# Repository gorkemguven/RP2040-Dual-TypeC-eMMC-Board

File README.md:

# RP2040 Dual Type-C eMMC High-Speed Development & Telemetry Board (PicoVault)

Bu proje; **Raspberry Pi RP2040** çift çekirdekli mikrodenetleyicisi, **Microchip USB2244** yüksek hızlı USB 2.0 köprüsü ve **Micron eMMC (BGA-153)** yüksek yoğunluklu depolama birimini tek bir 4 katmanlı PCB üzerinde birleştiren endüstriyel standartta bir akıllı veri depolama ve geliştirme kartıdır.

Kart; çift USB Type-C mimarisi, donanımsal güç telemetrisi (çift INA226 akım/voltaj monitörü ve Kelvin algılama), yüksek doğruluklu sıcaklık izleme (TMP119) ve durum bilgilendirme OLED ekran arayüzü ile hem bağımsız bir yüksek hızlı USB flash sürücü hem de derinlemesine analiz yapabilen bir gömülü geliştirme platformu olarak tasarlanmıştır.

---

## 📌 Öne Çıkan Özellikler

* **Çift Çekirdekli İşlem Gücü:** Raspberry Pi RP2040 (Çift ARM Cortex-M0+ @ 133 MHz, 264 KB dahili SRAM).
* **Yüksek Hızlı Depolama (eMMC):** Micron BGA-153 paket yüksek hızlı eMMC bellek modülü.
* **Yüksek Hızlı USB Köprüsü:** Microchip USB2244 High-Speed USB 2.0 SD/eMMC kontrolcüsü (480 Mbps).
* **Boot Flash Belleği:** 128 Mb (16 MB) Winbond W25Q128JVSIC QSPI Flash[cite: 3].
* **Çift USB Type-C Portu:**
  * *Port 1 (Depolama):* USB2244 üzerinden doğrudan eMMC'ye yüksek hızlı USB 2.0 (480 Mbps) erişim.
  * *Port 2 (MCU / Telemetri):* RP2040 Full-Speed USB arayüzü (veri kaydı, programlama, seri haberleşme).
* **Donanımsal Güç ve Sıcaklık Telemetrisi:**
  * 2x **TI INA226** I2C güç/gerilim/akım izleme entegresi (2 mΩ 4-terminalli Kelvin şönt algılama)[cite: 7, 8].
  * 1x **TI TMP119** ±0.1°C yüksek hassasiyetli dijital sıcaklık sensörü[cite: 4].
  * 0.96'' I2C SSD1306 OLED ekran konnektörü ile anlık telemetri gösterimi[cite: 5].
* **Genişleme Portu:** Harici SPI, I2C, UART ve GPIO erişimi sağlayan 12-pin breakout soketi[cite: 1].
* **Üretim Optimizasyonu:** Maliyet düşürmek amacıyla tüm kritik bileşenler tek yüzeye (Single-Sided Assembly) yerleştirilmiştir.

---

## 📐 Donanım Mimarisi ve Yüksek Hızlı Sinyal Bütünlüğü

### 1. USB2244 – eMMC (BGA-153) 8-Bit Yüksek Hızlı Veri Yolu (Zero-Skew Matching)
USB2244 ile eMMC arasındaki 8-bit paralel veri yolu (MMC standardı), yüksek frekanslı çalışma modlarında saat ve veri gecikmelerini (skew) sıfırlamak için **tam 35.66 mm** boyuna meander teknikleriyle kusursuz şekilde eşitlenmiştir:
* **Tüm Hatların Uzunluğu:** Tam olarak **35.66 mm**
* **Maksimum Skew / Sapma:** **0.00 mm (0.00 ps)**
* **Hat Empedansı:** Katman 2 kesintisiz GND referansı üzerinden 50 Ω mikroşerit geometri.

| Sinyal Adı | Pin Adı | Rotalama Türü | Empedans | Net Hat Uzunluğu | Skew (Fark) |
| :--- | :--- | :--- | :---: | :---: | :---: |
| **`MMC_CLK`** | Clock (Saat) | GND Referanslı Mikroşerit | 50 Ω | **35.66 mm** | Referans |
| **`MMC_CMD`** | Command / Response | Çift Yönlü Kontrol | 50 Ω | **33.44 mm** | **2.22 mm** |
| **`MMCDA0`** | Data Bit 0 | Yüksek Hızlı Veri | 50 Ω | **35.66 mm** | **0.00 mm** |
| **`MMCDA1`** | Data Bit 1 | Yüksek Hızlı Veri | 50 Ω | **35.66 mm** | **0.00 mm** |
| **`MMCDA2`** | Data Bit 2 | Yüksek Hızlı Veri | 50 Ω | **35.66 mm** | **0.00 mm** |
| **`MMCDA3`** | Data Bit 3 | Yüksek Hızlı Veri | 50 Ω | **35.66 mm** | **0.00 mm** |
| **`MMCDA4`** | Data Bit 4 | Yüksek Hızlı Veri | 50 Ω | **35.56 mm** | **0.10 mm** |
| **`MMCDA5`** | Data Bit 5 | Yüksek Hızlı Veri | 50 Ω | **35.66 mm** | **0.00 mm** |
| **`MMCDA6`** | Data Bit 6 | Yüksek Hızlı Veri | 50 Ω | **35.66 mm** | **0.00 mm** |
| **`MMCDA7`** | Data Bit 7 | Yüksek Hızlı Veri | 50 Ω | **35.66 mm** | **0.00 mm** |
| **`MMC_RST_N`** | Hardware Reset | Filtrelenmiş Kontrol | 50 Ω | Bağımsız | Asenkron |

*(Not: Bu 10 hattın tamamında sıfır kör hat (stub-free) prensibi uygulanmış ve BGA çıkışlarında dönüş akımının bütünlüğü korunmuştur).*

### 2. QSPI Flash Yönlendirme ve Gecikme Eşleme (Length Matching)
Flash bellek yolu, 133 MHz saat hızında okuma/yazma kararlılığını garanti altına almak için 50 Ω kontrollü empedans ve katı boy eşleme kurallarıyla yönlendirilmiştir:
* **Tüm Sinyal Hatları:** Eşit parazitik yük için tam olarak **2 via** kullanılarak alt katmana geçirilmiştir.
* **Saat Hattı Referansı (`QSPI_SCLK`):** 24.54 mm
* **Veri Hatları Skew Dengesi:**
  * `QSPI_SD0`: 26.10 mm (ΔL = +1.56 mm)
  * `QSPI_SD1`: 25.76 mm (ΔL = +1.22 mm)
  * `QSPI_SD2`: 27.14 mm (ΔL = +2.60 mm)
  * `QSPI_SD3`: 24.81 mm (ΔL = +0.27 mm)
  * `QSPI_SS`: 22.57 mm (ΔL = -1.97 mm)
* **Stub İzolasyonu:** 1 kΩ (`R504`) BOOTSEL izolasyon direnci ve 10 kΩ (`R505`) pull-up direnci, yüksek hızlı `/CS` hattında açık devre yansıması oluşturmaması için doğrudan Flash entegresinin Pin 1 bacağının 1 mm yakınına konumlandırılmıştır[cite: 3].

### 3. Analog Kristal Osilatör Bölgesi (EMC & Noise Immunity)
* **Rezonatör:** RP2040 için 12 MHz SMD kristal ve 15 pF yük kapasitörleri.
* **Sönümleme:** `XOUT` bacağında 1 kΩ seri akım sınırlama/sönümleme direnci.
* **Gürültü Koruması (Keepout Area):** Kristalin ve yük kapasitörlerinin altındaki tüm katmanlar dijital sinyallerden arındırılmıştır[cite: 2]. `SPI_SCK` ve hızlı GPIO hatları kristal sınırının dışına taşınmış; Layer 2 üzerinde kesintisiz katı GND bakırı ve kristal gövde pinlerinde (Pin 2 ve 4) çift via topraklaması uygulanmıştır[cite: 2].

### 4. eMMC Güç Dağıtım Ağı (PDN - Decoupling Network)
* Tek yüzeyli montaj gereği dekuplaj kapasitörleri BGA-153 paketinin çevresine optimize mesafelerle dizilmiştir:
  * **VDDIM (`C2`):** 4.6 mm hat, 2 via, 100 nF + 1 µF çift filtreleme.
  * **VCC (`E6, F5` & `J10, K9`):** 100 nF, 1 µF ve 2.2 µF kapasitör grupları (6.5–8.0 mm).
  * **VCCQ (`C6` & `M4, N4, P3, P5`):** Çekirdek VCC hattındaki anahtarlama gürültüsünden etkilenmemesi için yüzeyde VCC'den izole edilmiş; ana +3.3V düzleminden yerel 2.2 µF kapasitörlerle beslenmiştir.

### 5. Kelvin Akım Algılama ve I2C Topolojisi
* **4-Wire Kelvin Sensing:** 2 mΩ şönt dirençlerin gerilim algılama pinleri (`IN+` ve `IN-`), yüksek akım taşıyan güç pedlerinden bağımsız olarak alt katmandan diferansiyel çift mantığıyla INA226 entegrelerine taşınmıştır[cite: 7, 9].
* **Adresleme:**
  * `IC702` (INA226 #1): A1 = GND, A0 = GND → **0x40**[cite: 8]
  * `IC703` (INA226 #2): A1 = GND, A0 = +3.3V → **0x41**[cite: 8]
* **I2C Veriyolu:** RP2040'tan çıkan tek veriyolu TMP119 (3.5 cm), OLED (5.3 cm), INA1 (7.0 cm) ve INA2 (8.8 cm) arayüzlerini beslemektedir[cite: 4, 5, 8]. Hat empedansı TMP119 yakınındaki 5 kΩ pull-up dirençleri (`R701`, `R702`) ile sürülmekte ve toplam veriyolu kapasitansı 400 pF standardının oldukça altında kalmaktadır[cite: 4, 6].

---

## 🔌 Bağlantı Portları ve Pin Şeması

### 1. J803 Genişleme Konnektörü (1x12 Pin Header)
Harici çevre birimleri ve geliştirme modülleri için dışarı çıkarılmış arayüzdür[cite: 1]:

| Pin | Sinyal Adı | Tip | Rotalama Detayı | Açıklama |
| :---: | :--- | :--- | :--- | :--- |
| **1** | `+3.3V` | Güç | Çift via ile +3.3V katmanına bağlı | Harici modül beslemesi |
| **2** | `UART_TX` | Çıkış | 50.00 mm (0 via) | Seri konsol / Debug çıkışı |
| **3** | `UART_RX` | Giriş | 49.80 mm (0 via) | Seri konsol giriş |
| **4** | `SPI_SCK` | Çıkış | 42.17 mm (2 via) | Harici SPI Saat hattı |
| **5** | `SPI_MOSI` | Çıkış | 41.52 mm (2 via) | Harici SPI Veri çıkışı |
| **6** | `SPI_MISO` | Giriş | 41.83 mm (2 via) | Harici SPI Veri girişi |
| **7** | `SPI_CS` | Çıkış | 41.92 mm (2 via) | Harici SPI Çip seçimi |
| **8** | `I2C_SDA` | Çift Yönlü | 57.08 mm (2 via) | Harici I2C Veri hattı |
| **9** | `I2C_SCL` | Çıkış | 56.62 mm (2 via) | Harici I2C Saat hattı |
| **10** | `GPIO14` | Giriş/Çıkış | 43.70 mm (2 via) | Genel amaçlı GPIO / Kesme |
| **11** | `GPIO15` | Giriş/Çıkış | 43.87 mm (2 via) | Genel amaçlı GPIO / Kesme |
| **12** | `GND` | Güç | Çift via ile ana GND katmanına bağlı | Ortak sistem toprağı |

*(Not: SPI veri yolu hatları arasındaki maksimum skew yalnızca 0.65 mm'dir; bu sayede yüksek hızlı SPI ekranlar veya harici modüllerle sorunsuz çalışır).*

### 2. Programlama ve Hata Ayıklama (Debug)
* **SWD Portu (`SWCLK`, `SWD`, `GND`):** Canlı hata ayıklama (step-by-step breakpoint debug) ve doğrudan bellek programlama arayüzüdür.
  * `SWCLK` (22.60 mm) ve `SWD` (23.00 mm) hatları tam simetrik ve 0.40 mm toleransla eşlenmiştir.
* **RUN (Donanımsal Reset):** 100 nF kapasitör ve 10 kΩ pull-up direnci ile çipin 3.66 mm dibinde filtrelenmiştir.
* **J502 (`USB_BOOT`):** 1 kΩ direnç üzerinden Flash `/CS` hattını toprağa çekerek RP2040'ı dahili ROM UF2 Mass Storage bootloader moduna geçirir[cite: 3].

---

## 🗂️ Depo Dosya Yapısı

```text
├── hardware/
│   ├── schematics/          # KiCad hiyerarşik şematik dosyaları (.kicad_sch)
│   ├── layout/              # KiCad 4-katman PCB yerleşim dosyaları (.kicad_pcb)
│   ├── libraries/           # Projeye özel kütüphane sembol ve ayak izleri (Footprints)
│   └── outputs/
│       ├── gerbers/         # Üretim için RS-274X Gerber ve Drill dosyaları
│       └── bom/             # Parça listesi (Bill of Materials - .csv)
├── docs/
│   ├── schematics.pdf       # Tek tıkla incelenebilir tam şematik PDF çıktısı
│   ├── 3d_renders/          # Kartın ön/arka 3D görsel renderları
│   └── datasheets/          # Kritik entegre dökümanları (USB2244, INA226, TMP119, W25Q128)
├── .gitignore               # KiCad geçici ve yedek dosyalarını filtreler
└── README.md                # Proje dokümantasyonu

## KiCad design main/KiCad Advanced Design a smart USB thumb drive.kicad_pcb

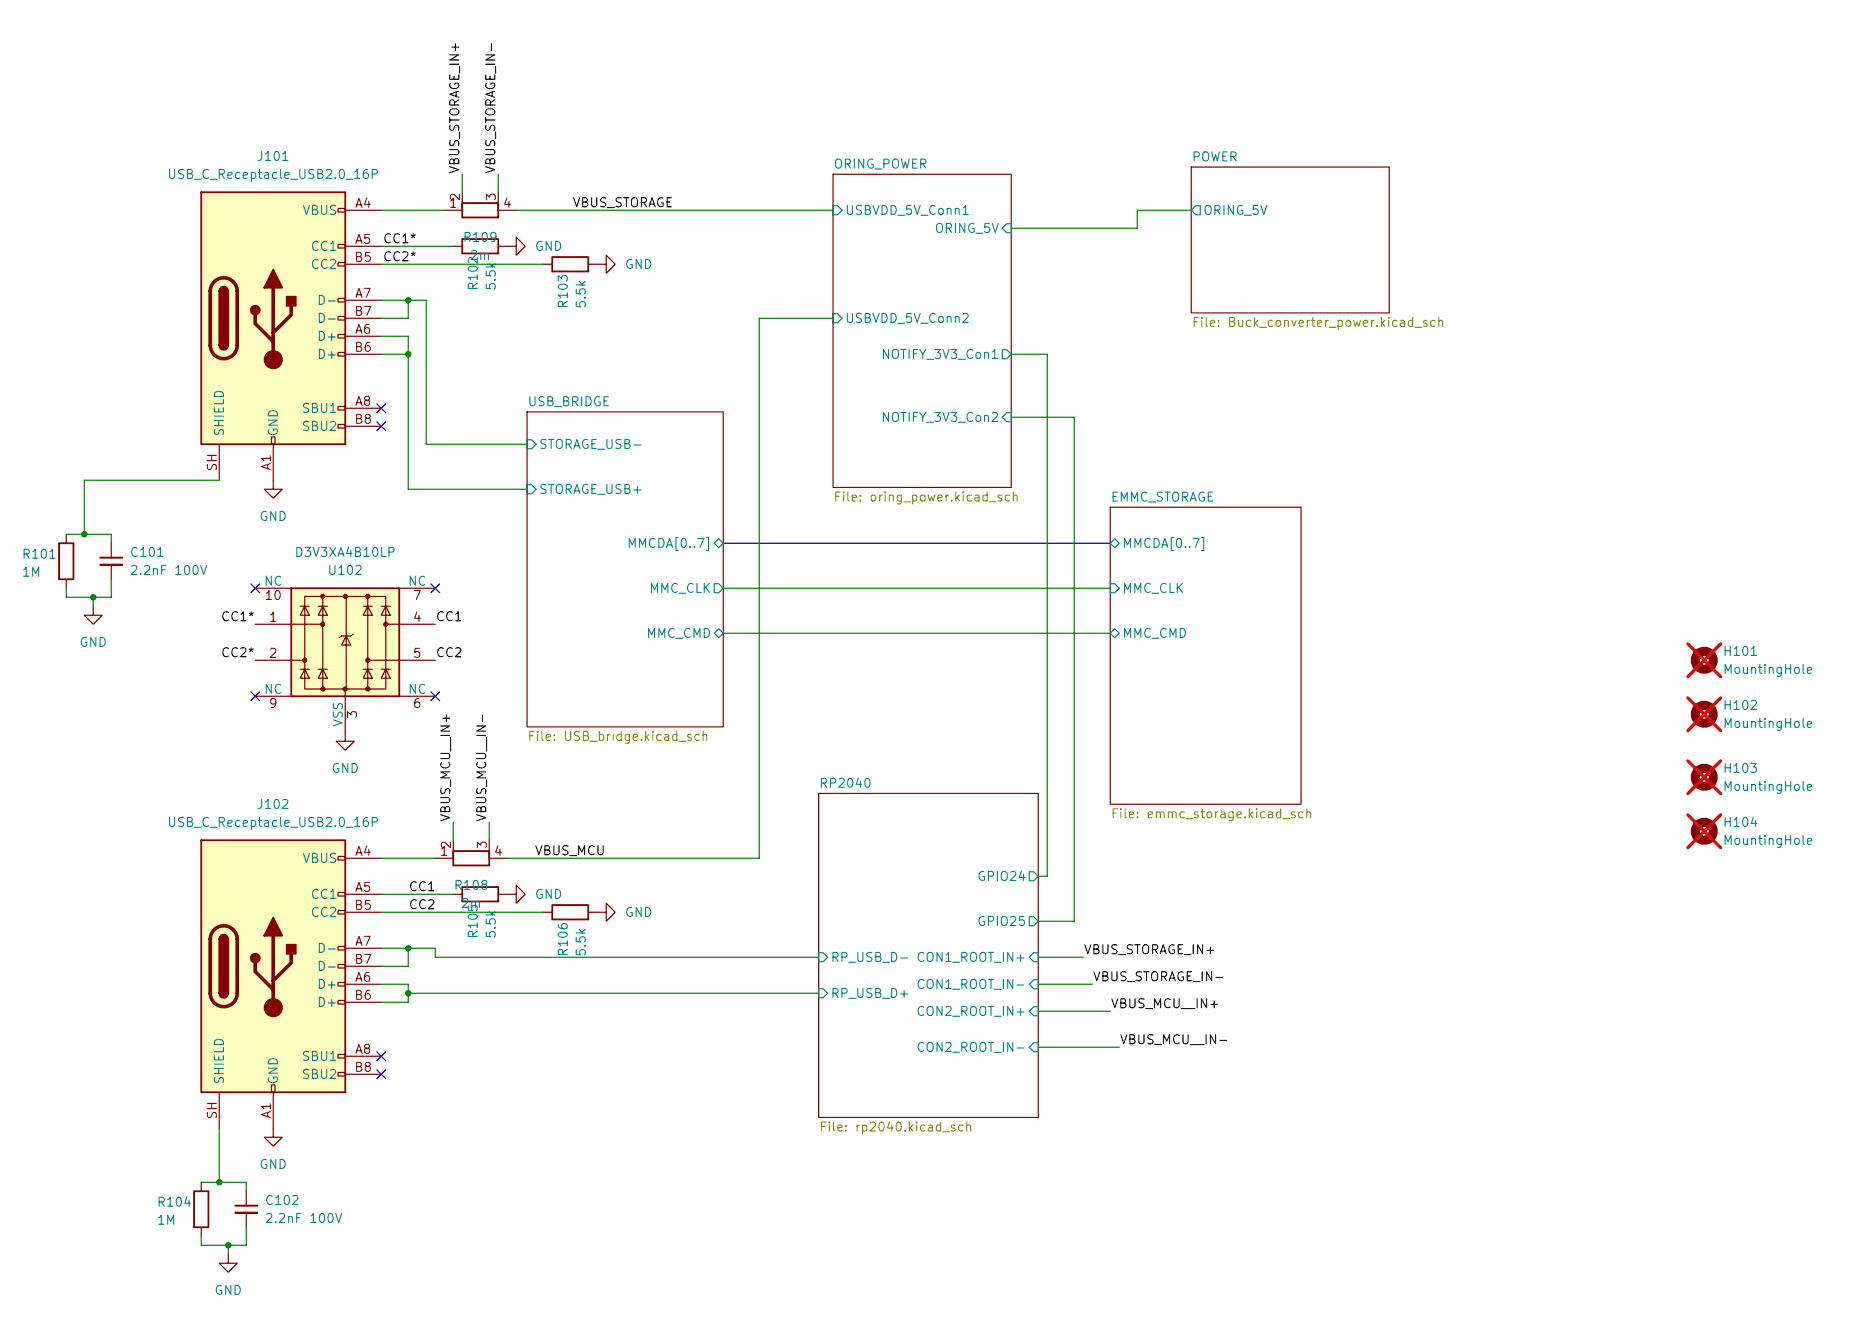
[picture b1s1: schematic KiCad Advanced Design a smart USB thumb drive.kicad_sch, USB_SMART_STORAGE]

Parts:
C101, C102: 2.2nF 100V; C_0603_1608Metric
H101, H102, H103, H104: MountingHole; MountingHole_2.2mm_M2; not fitted
J101, J102: USB_C_Receptacle_USB2.0_16P; USB_C_Receptacle_XKB_U262-16XN-4BVC11
R101, R104: 1M; R_0402_1005Metric
R102, R103, R105, R106: 5.5k; R_0402_1005Metric
R108, R109: 2m; R_Shunt_Ohmite_LVK12
U102: D3V3XA4B10LP; Diodes_UDFN-10_1x2.5mm_P0.5mm

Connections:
/CC1: J102.A5 (CC1), R105.1, U102.4
/CC1*: J101.A5 (CC1), R102.1, U102.1
/CC2: J102.B5 (CC2), R106.1, U102.5
/CC2*: J101.B5 (CC2), R103.1, U102.2
/RP2040/RP_USB_D+: J102.A6 (D+), J102.B6 (D+); also elsewhere on the board
/RP2040/RP_USB_D-: J102.A7 (D-), J102.B7 (D-); also elsewhere on the board
/USB_BRIDGE/STORAGE_USB+: J101.A6 (D+), J101.B6 (D+); also elsewhere on the board
/USB_BRIDGE/STORAGE_USB-: J101.A7 (D-), J101.B7 (D-); also elsewhere on the board
/VBUS_MCU: R108.4; also elsewhere on the board
/VBUS_MCU__IN+: R108.2; also elsewhere on the board
/VBUS_MCU__IN-: R108.3; also elsewhere on the board
/VBUS_STORAGE: R109.4; also elsewhere on the board
/VBUS_STORAGE_IN+: R109.2; also elsewhere on the board
/VBUS_STORAGE_IN-: R109.3; also elsewhere on the board
GND: C101.2, C102.2, J101.A1 (GND), J101.A12 (GND), J101.B1 (GND), J101.B12 (GND), J102.A1 (GND), J102.A12 (GND), J102.B1 (GND), J102.B12 (GND), R101.2, R102.2, R103.2, R104.2, R105.2, R106.2, U102.3 (VSS), U102.8 (VSS); also elsewhere on the board
unnamed: C101.1, J101.SH (SHIELD), R101.1
unnamed: J101.A4 (VBUS), J101.A9 (VBUS), J101.B4 (VBUS), J101.B9 (VBUS), R109.1
unnamed: C102.1, J102.SH (SHIELD), R104.1
unnamed: J102.A4 (VBUS), J102.A9 (VBUS), J102.B4 (VBUS), J102.B9 (VBUS), R108.1

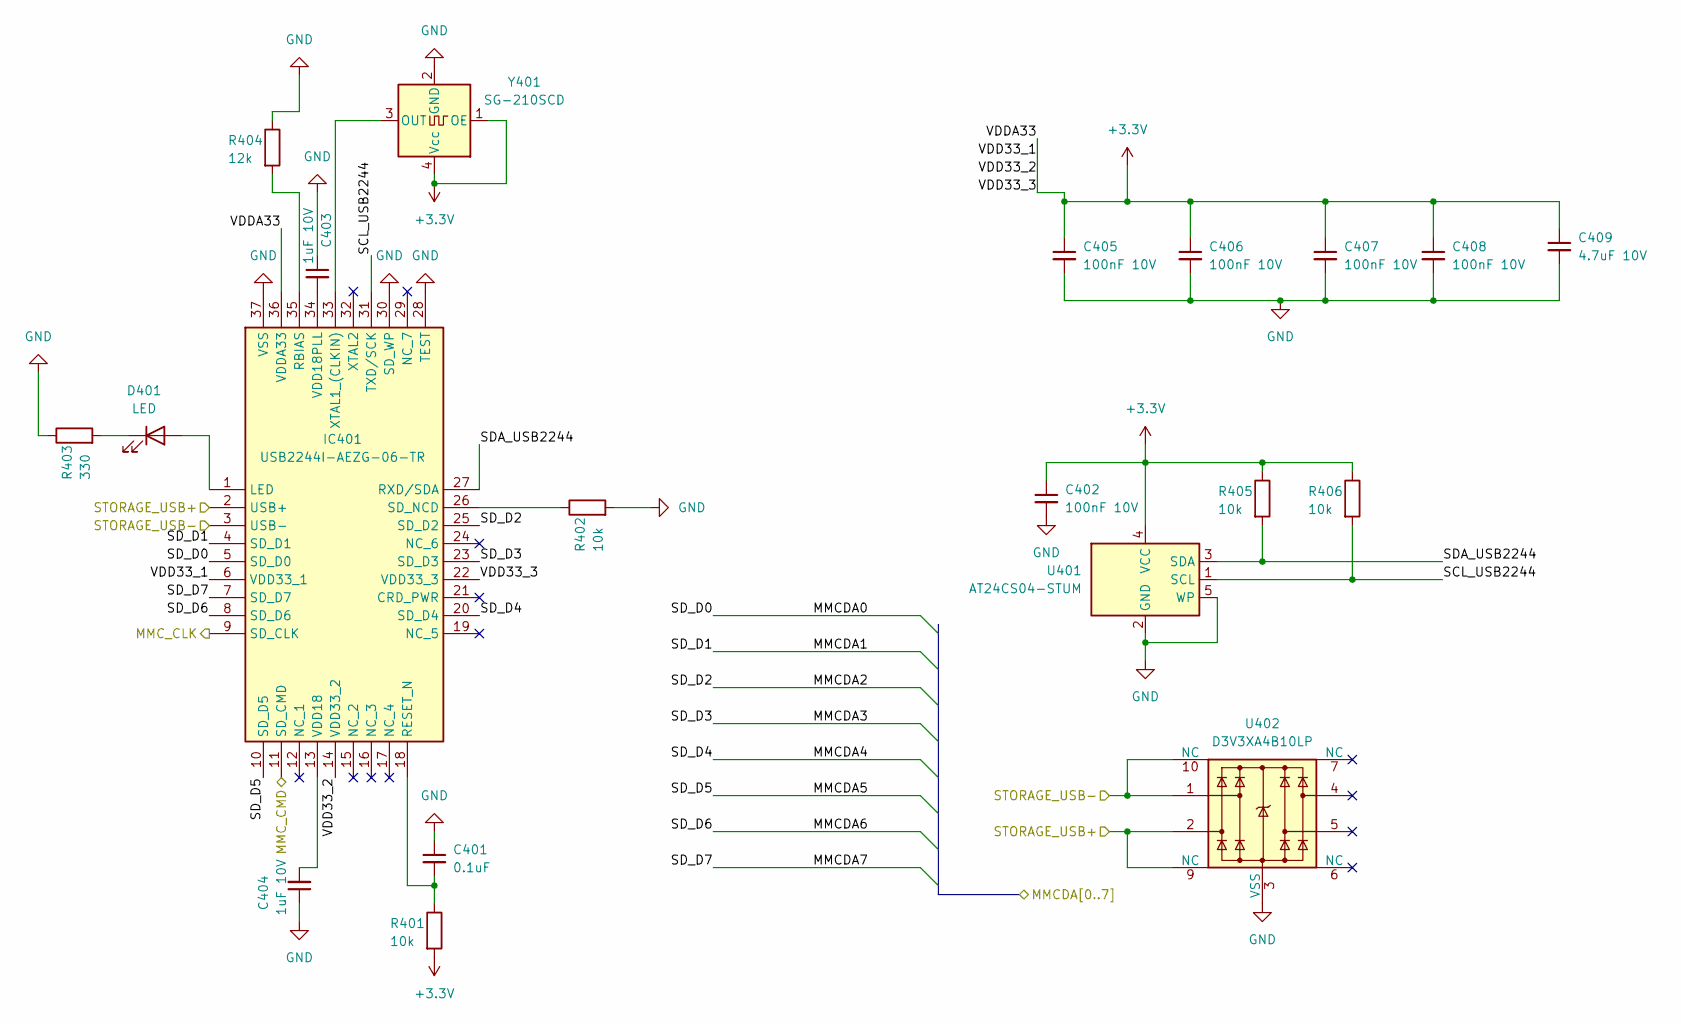
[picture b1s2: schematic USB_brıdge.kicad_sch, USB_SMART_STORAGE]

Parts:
C401: 0.1uF; C_0402_1005Metric
C402, C405, C406, C407, C408: 100nF 10V; C_0402_1005Metric
C403, C404: 1uF 10V; C_0603_1608Metric
C409: 4.7uF 10V; C_0603_1608Metric
D401: LED; LED_0603_1608Metric
IC401: USB2244I-AEZG-06-TR; QFN50P600X600X90-37N-D; Manufacturer_Part_Number USB2244I-AEZG-06-TR; Mouser Part Number 579-USB2244IAEZG06TR
R401, R402, R405, R406: 10k; R_0402_1005Metric
R403: 330; R_0402_1005Metric
R404: 12k; R_0402_1005Metric
U401: AT24CS04-STUM; SOT-23-5
U402: D3V3XA4B10LP; Diodes_UDFN-10_1x2.5mm_P0.5mm
Y401: SG-210SCD; Oscillator_SMD_SeikoEpson_SG210-4Pin_2.5x2.0mm

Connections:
+3.3V: C402.1, C405.1, C406.1, C407.1, C408.1, C409.1, IC401.6 (VDD33_1), IC401.14 (VDD33_2), IC401.22 (VDD33_3), IC401.36 (VDDA33), R401.2, R405.1, R406.1, U401.4 (VCC), Y401.1 (OE), Y401.4 (Vcc); also elsewhere on the board
/EMMC_STORAGE/MMCDA0: IC401.5 (SD_D0); also elsewhere on the board
/EMMC_STORAGE/MMCDA1: IC401.4 (SD_D1); also elsewhere on the board
/EMMC_STORAGE/MMCDA2: IC401.25 (SD_D2); also elsewhere on the board
/EMMC_STORAGE/MMCDA3: IC401.23 (SD_D3); also elsewhere on the board
/EMMC_STORAGE/MMCDA4: IC401.20 (SD_D4); also elsewhere on the board
/EMMC_STORAGE/MMCDA5: IC401.10 (SD_D5); also elsewhere on the board
/EMMC_STORAGE/MMCDA6: IC401.8 (SD_D6); also elsewhere on the board
/EMMC_STORAGE/MMCDA7: IC401.7 (SD_D7); also elsewhere on the board
/EMMC_STORAGE/MMC_CLK: IC401.9 (SD_CLK); also elsewhere on the board
/EMMC_STORAGE/MMC_CMD: IC401.11 (SD_CMD); also elsewhere on the board
/USB_BRIDGE/SCL_USB2244: IC401.31 (TXD/SCK), R406.2, U401.1 (SCL)
/USB_BRIDGE/SDA_USB2244: IC401.27 (RXD/SDA), R405.2, U401.3 (SDA)
/USB_BRIDGE/STORAGE_USB+: IC401.2 (USB+), U402.2, U402.9 (NC); also elsewhere on the board
/USB_BRIDGE/STORAGE_USB-: IC401.3 (USB-), U402.1, U402.10 (NC); also elsewhere on the board
GND: C401.1, C402.2, C403.1, C404.1, C405.2, C406.2, C407.2, C408.2, C409.2, IC401.28 (TEST), IC401.30 (SD_WP), IC401.37 (VSS), R402.2, R403.1, R404.1, U401.2 (GND), U401.5 (WP), U402.3 (VSS), U402.8 (VSS), Y401.2 (GND); also elsewhere on the board
unnamed: D401.2 (A), IC401.1 (LED)
unnamed: D401.1 (K), R403.2
unnamed: IC401.35 (RBIAS), R404.2
unnamed: C401.2, IC401.18 (RESET_N), R401.1
unnamed: IC401.26 (SD_NCD), R402.1
unnamed: C404.2, IC401.13 (VDD18)
unnamed: C403.2, IC401.34 (VDD18PLL)
unnamed: IC401.33 (XTAL1_(CLKIN)), Y401.3 (OUT)

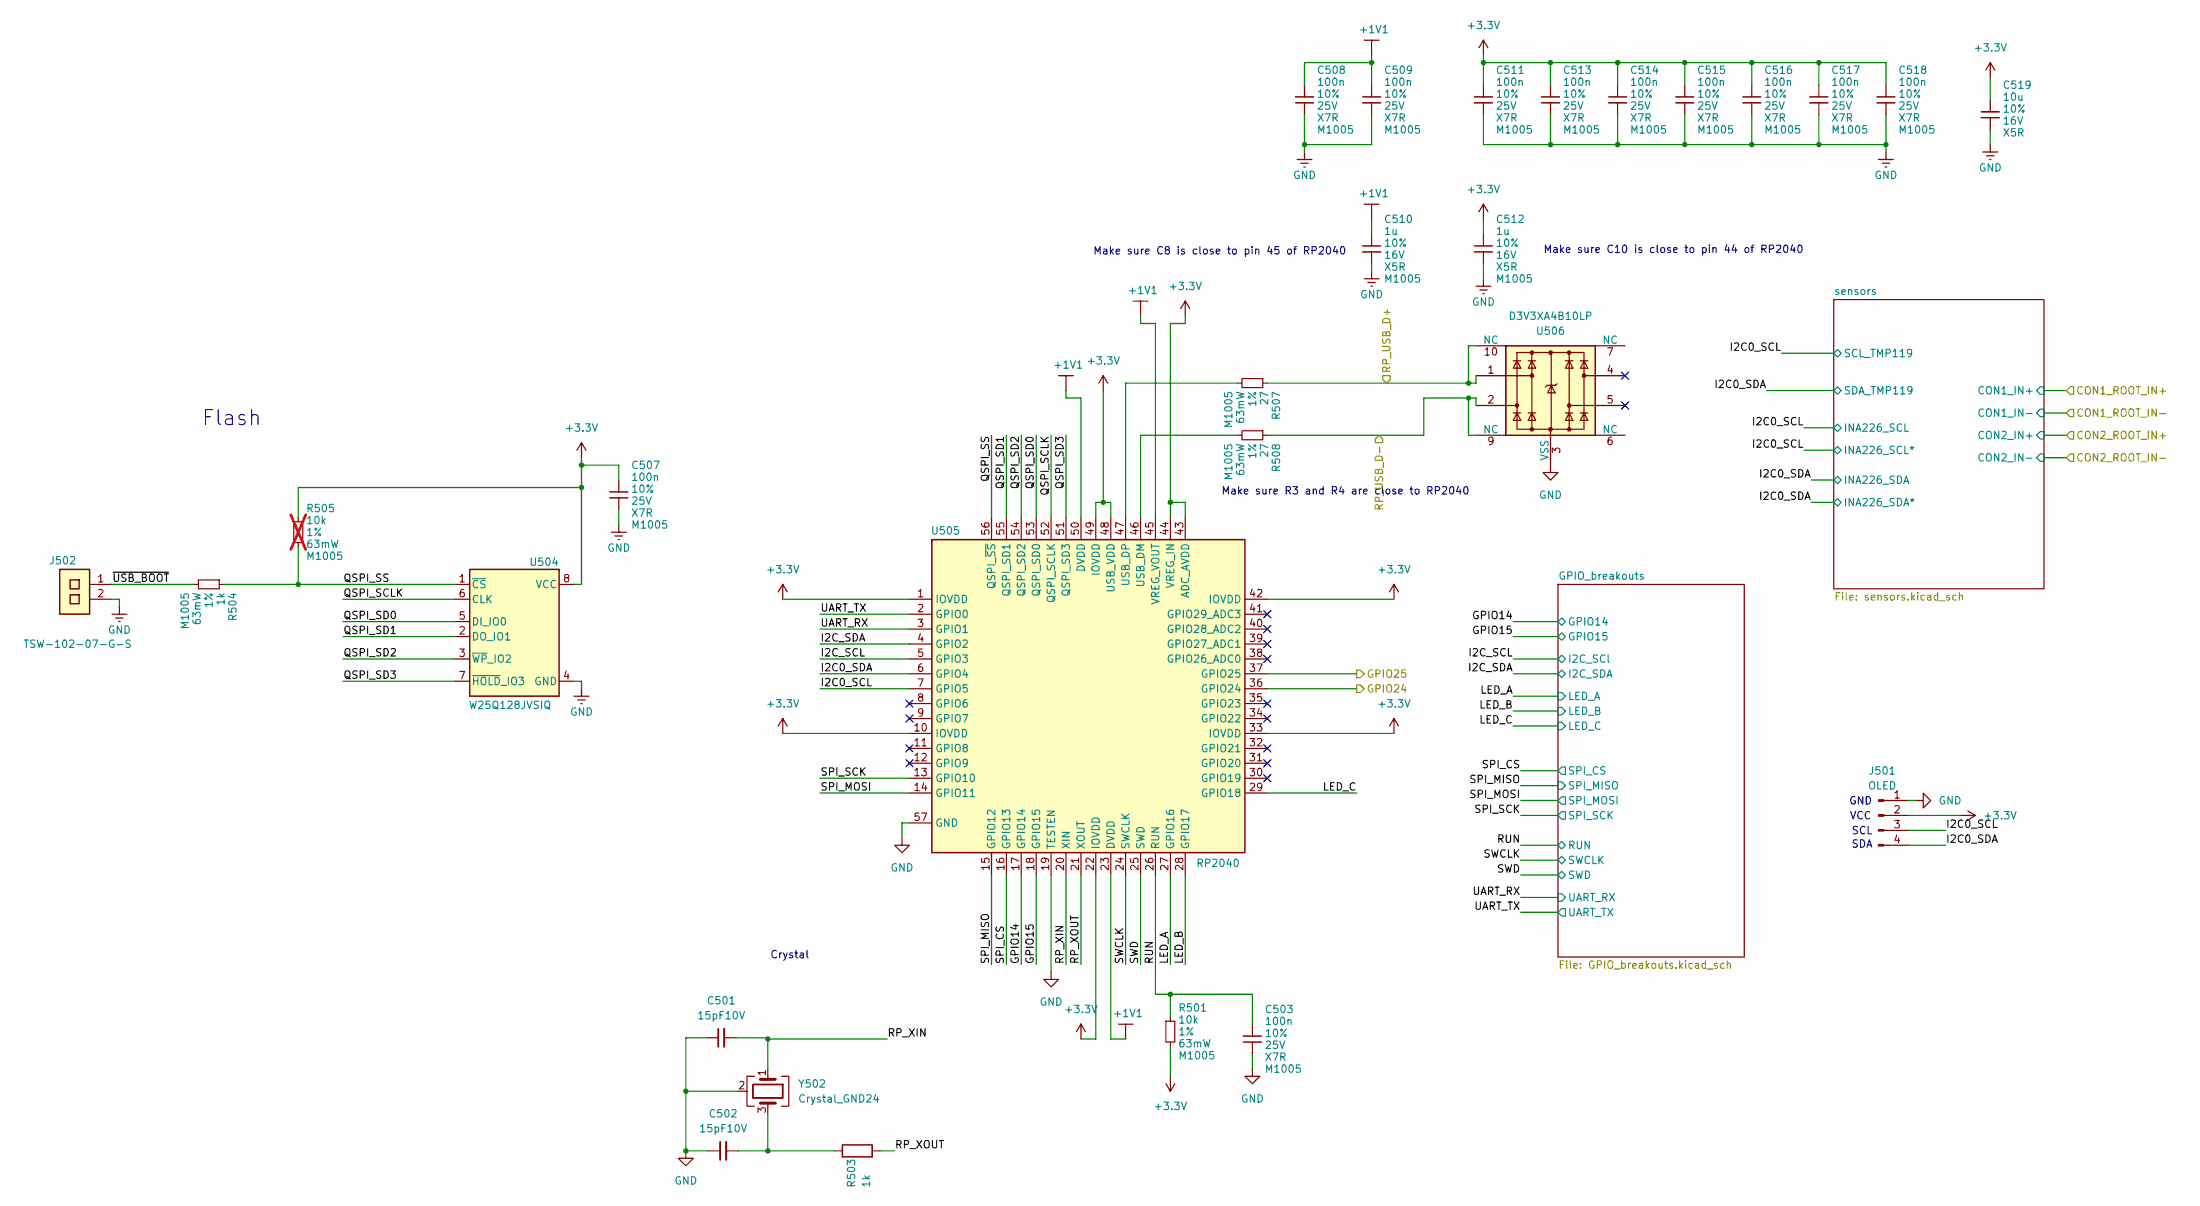
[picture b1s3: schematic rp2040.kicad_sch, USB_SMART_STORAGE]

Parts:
C501, C502: 15pF10V; C_0402_1005Metric
C503, C507, C508, C509, C511, C513, C514, C515, C516, C517, C518: 100n; C_0402_1005Metric; voltage 25V; tolerance 10%; part_uid RP-01BJ9Y-KRGF41
C510, C512: 1u; C_0603_1608Metric; voltage 16V; tolerance 10%; part_uid RP-01GYSK-L7FEKV
C519: 10u; C_0603_1608Metric; voltage 16V; tolerance 10%; part_uid RP-01GYSK-AVBE41
J501: OLED; PinHeader_1x04_P2.54mm_Vertical
J502: TSW-102-07-G-S; TE_440054-2_1x02_P2.00mm_Vertical; part_uid RP-01JV5X-LY21H5
R501: 10k; R_0402_1005Metric; tolerance 1%; voltage 50V; part_uid RP-019A1P-53DHSX
R503: 1k; R_0402_1005Metric
R504: 1k; R_0402_1005Metric; tolerance 1%; voltage 50V; part_uid RP-019A1P-4Z6ZWY
R505: 10k; R_0402_1005Metric; tolerance 1%; voltage 50V; part_uid RP-019A1P-53DHSX; not fitted
R507, R508: 27; R_0402_1005Metric; tolerance 1%; voltage 50V; part_uid RP-01C89V-LTEYC4
U504: W25Q128JVSIQ; voltage 2.7-3.6V; part_uid RP-01JWD4-F1H4N9
U505: RP2040; QFN-56-1EP_7x7mm_P0.4mm_EP3.2x3.2mm; part_uid RP-01EKHS-ZTKTEH
U506: D3V3XA4B10LP; Diodes_UDFN-10_1x2.5mm_P0.5mm
Y502: Crystal_GND24; Crystal_SMD_Abracon_ABM8G-4Pin_3.2x2.5mm

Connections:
+1V1: C508.1, C509.1, C510.1, U505.23 (DVDD), U505.45 (VREG_VOUT), U505.50 (DVDD)
+3.3V: C507.1, C511.1, C512.1, C513.1, C514.1, C515.1, C516.1, C517.1, C518.1, C519.1, J501.2, R501.2, R505.1, U504.8 (VCC), U505.1 (IOVDD), U505.10 (IOVDD), U505.22 (IOVDD), U505.33 (IOVDD), U505.42 (IOVDD), U505.43 (ADC_AVDD), U505.44 (VREG_IN), U505.48 (USB_VDD), U505.49 (IOVDD); also elsewhere on the board
/ORING_POWER/NOTIFY_3V3_Con1: U505.36 (GPIO24); also elsewhere on the board
/ORING_POWER/NOTIFY_3V3_Con2: U505.37 (GPIO25); also elsewhere on the board
/RP2040/GPIO14: U505.17 (GPIO14); also elsewhere on the board
/RP2040/GPIO15: U505.18 (GPIO15); also elsewhere on the board
/RP2040/I2C0_SCL: J501.3, U505.7 (GPIO5); also elsewhere on the board
/RP2040/I2C0_SDA: J501.4, U505.6 (GPIO4); also elsewhere on the board
/RP2040/I2C_SCL: U505.5 (GPIO3); also elsewhere on the board
/RP2040/I2C_SDA: U505.4 (GPIO2); also elsewhere on the board
/RP2040/LED_A: U505.27 (GPIO16); also elsewhere on the board
/RP2040/LED_B: U505.28 (GPIO17); also elsewhere on the board
/RP2040/LED_C: U505.29 (GPIO18); also elsewhere on the board
/RP2040/QSPI_SCLK: U504.6 (CLK), U505.52 (QSPI_SCLK)
/RP2040/QSPI_SD0: U504.5 (DI_IO0), U505.53 (QSPI_SD0)
/RP2040/QSPI_SD1: U504.2 (DO_IO1), U505.55 (QSPI_SD1)
/RP2040/QSPI_SD2: U504.3 (~WP_IO2), U505.54 (QSPI_SD2)
/RP2040/QSPI_SD3: U504.7 (~HOLD_IO3), U505.51 (QSPI_SD3)
/RP2040/QSPI_SS: R504.1, R505.2, U504.1 (~CS), U505.56 (QSPI_~SS)
/RP2040/RP_USB_D+: R507.1, U506.1, U506.10 (NC); also elsewhere on the board
/RP2040/RP_USB_D-: R508.1, U506.2, U506.9 (NC); also elsewhere on the board
/RP2040/RP_XIN: C501.2, U505.20 (XIN), Y502.1
/RP2040/RP_XOUT: R503.2, U505.21 (XOUT)
/RP2040/RUN: C503.1, R501.1, U505.26 (RUN); also elsewhere on the board
/RP2040/SPI_CS: U505.16 (GPIO13); also elsewhere on the board
/RP2040/SPI_MISO: U505.15 (GPIO12); also elsewhere on the board
/RP2040/SPI_MOSI: U505.14 (GPIO11); also elsewhere on the board
/RP2040/SPI_SCK: U505.13 (GPIO10); also elsewhere on the board
/RP2040/SWCLK: U505.24 (SWCLK); also elsewhere on the board
/RP2040/SWD: U505.25 (SWD); also elsewhere on the board
/RP2040/UART_RX: U505.3 (GPIO1); also elsewhere on the board
/RP2040/UART_TX: U505.2 (GPIO0); also elsewhere on the board
/RP2040/~USB_BOOT: J502.1, R504.2
GND: C501.1, C502.1, C503.2, C507.2, C508.2, C509.2, C510.2, C511.2, C512.2, C513.2, C514.2, C515.2, C516.2, C517.2, C518.2, C519.2, J501.1, J502.2, U504.4 (GND), U505.19 (TESTEN), U505.57 (GND), U506.3 (VSS), U506.8 (VSS), Y502.2 (G), Y502.4 (G); also elsewhere on the board
unnamed: C502.2, R503.1, Y502.3
unnamed: R508.2, U505.46 (USB_DM)
unnamed: R507.2, U505.47 (USB_DP)

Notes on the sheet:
Flash
SDA
Make sure C10 is close to pin 44 of RP2040
VCC
Crystal
Make sure C8 is close to pin 45 of RP2040
Make sure R3 and R4 are close to RP2040
SCL
GND

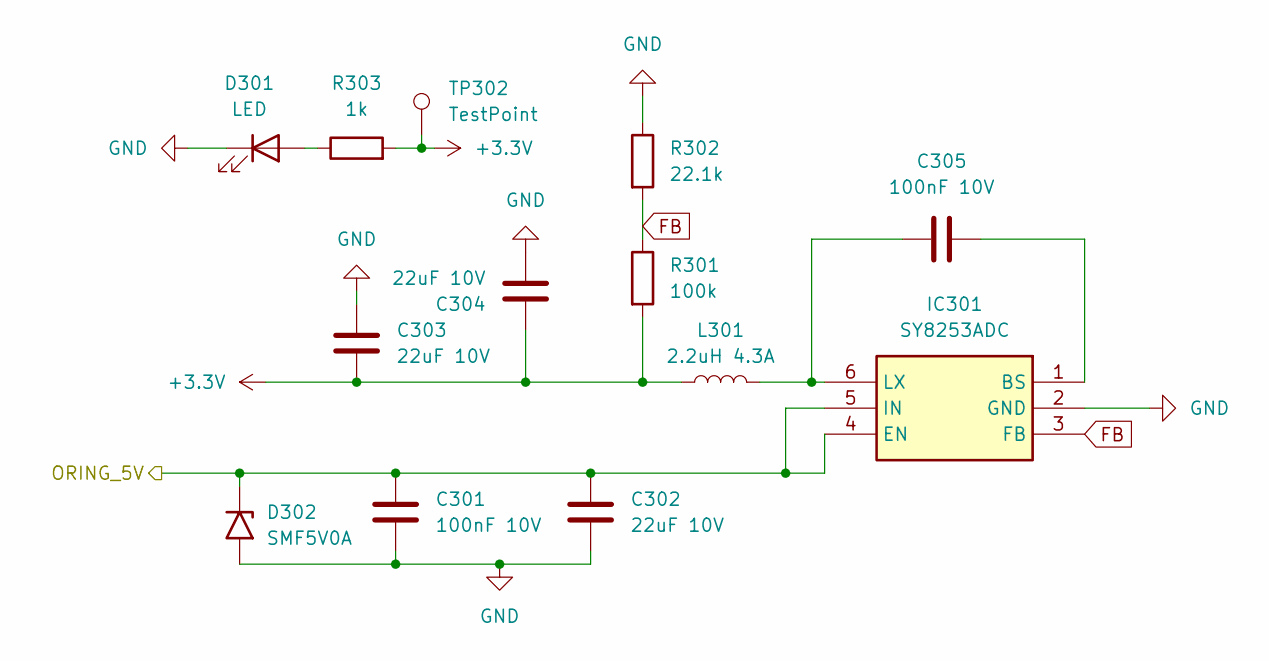
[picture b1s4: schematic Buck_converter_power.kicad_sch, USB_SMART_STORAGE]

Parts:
C301, C305: 100nF 10V; C_0402_1005Metric
C302, C303, C304: 22uF 10V; C_0805_2012Metric
D301: LED; LED_0603_1608Metric
D302: SMF5V0A; D_SMF
IC301: SY8253ADC; SOT95P285X100-6N; Manufacturer_Part_Number SY8253ADC
L301: 2.2uH 4.3A; L_Sunlord_SWPA4020S
R301: 100k; R_0402_1005Metric
R302: 22.1k; R_0402_1005Metric
R303: 1k; R_0402_1005Metric
TP302: TestPoint; TestPoint_Pad_D1.5mm

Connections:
+3.3V: C303.2, C304.1, L301.1, R301.2, R303.2, TP302.1 (1_1); also elsewhere on the board
/ORING_POWER/ORING_5V: C301.1, C302.1, D302.1 (A1), IC301.4 (EN), IC301.5 (IN); also elsewhere on the board
FB: IC301.3 (FB), R301.1, R302.2
GND: C301.2, C302.2, C303.1, C304.2, D301.1 (K), D302.2 (A2), IC301.2 (GND), R302.1; also elsewhere on the board
unnamed: D301.2 (A), R303.1
unnamed: C305.2, IC301.1 (BS)
unnamed: C305.1, IC301.6 (LX), L301.2

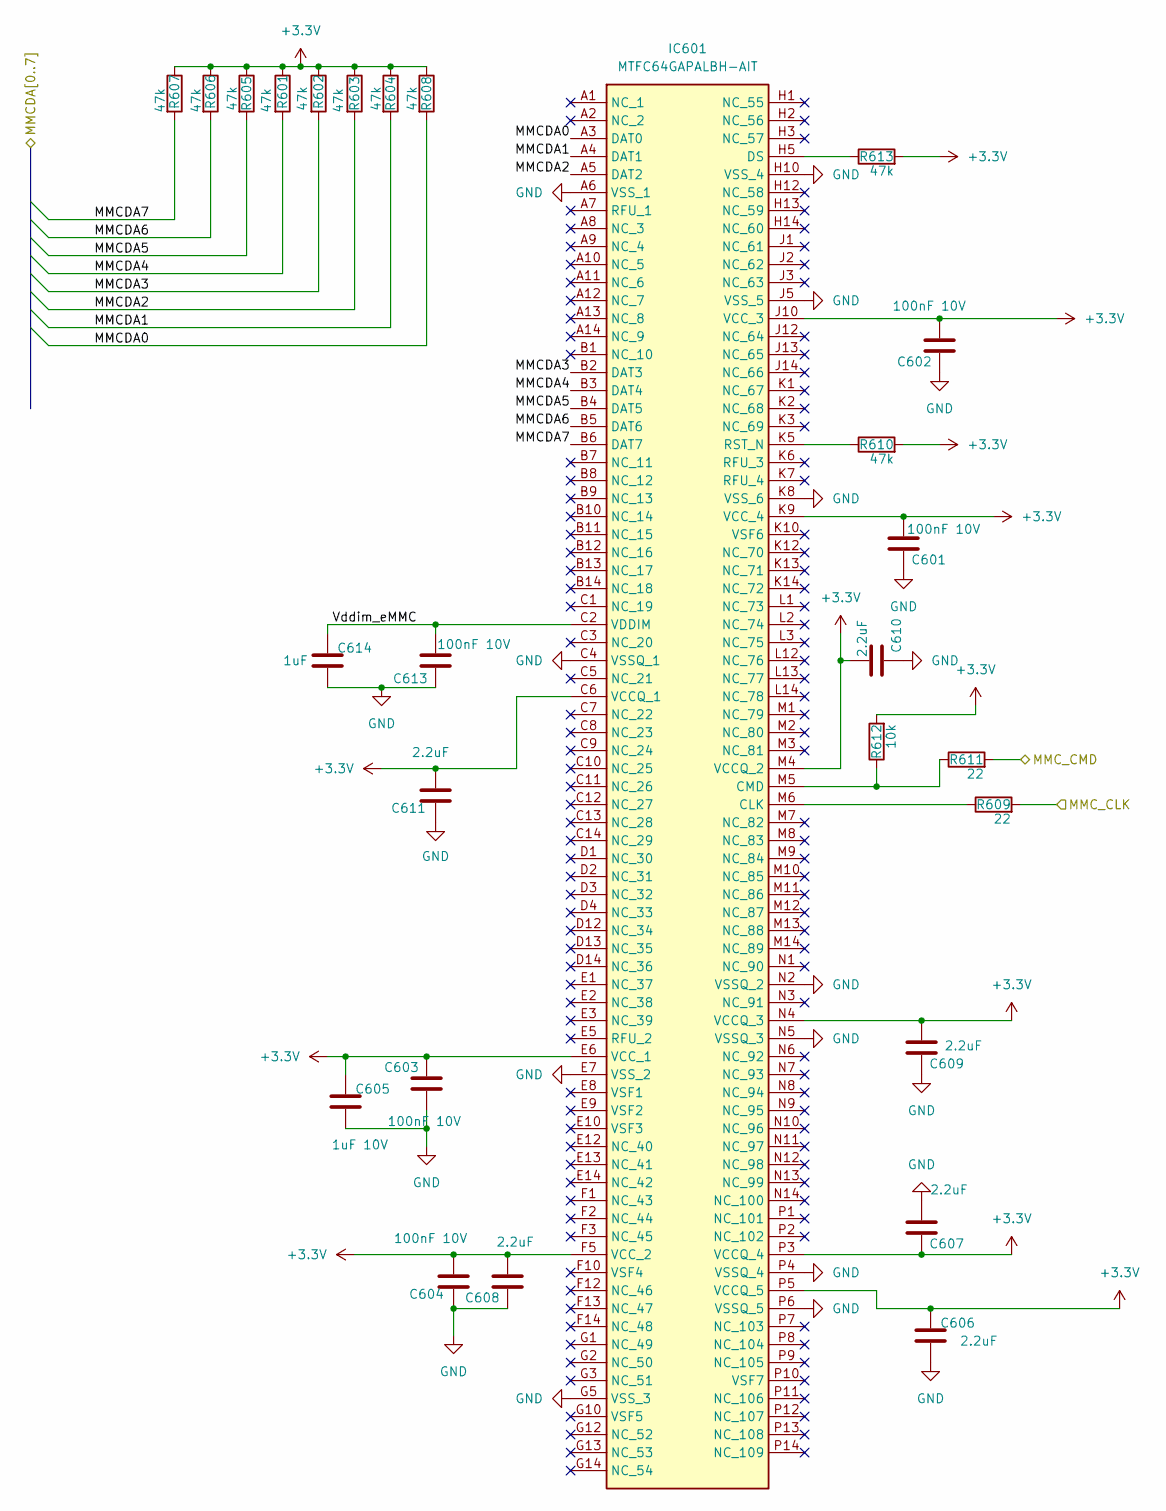
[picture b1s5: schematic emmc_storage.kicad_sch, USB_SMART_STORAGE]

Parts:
C601, C602, C603, C604, C613: 100nF 10V; C_0402_1005Metric
C605: 1uF 10V; C_0402_1005Metric
C606, C607, C608, C609, C610, C611: 2.2uF; C_0402_1005Metric
C614: 1uF; C_0402_1005Metric
IC601: MTFC64GAPALBH-AIT; Manufacturer_Part_Number MTFC64GAPALBH-AIT; Mouser Part Number 340-349211-TRAY
R601, R602, R603, R604, R605, R606, R607, R608, R610, R613: 47k; R_0402_1005Metric
R609, R611: 22; R_0402_1005Metric
R612: 10k; R_0402_1005Metric

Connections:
+3.3V: C601.1, C602.1, C603.2, C604.1, C605.2, C606.2, C607.2, C608.1, C609.1, C610.1, C611.1, IC601.C6 (VCCQ_1), IC601.E6 (VCC_1), IC601.F5 (VCC_2), IC601.J10 (VCC_3), IC601.K9 (VCC_4), IC601.M4 (VCCQ_2), IC601.N4 (VCCQ_3), IC601.P3 (VCCQ_4), IC601.P5 (VCCQ_5), R601.1, R602.1, R603.1, R604.1, R605.1, R606.1, R607.1, R608.1, R610.2, R612.2, R613.2; also elsewhere on the board
/EMMC_STORAGE/MMCDA0: IC601.A3 (DAT0), R608.2; also elsewhere on the board
/EMMC_STORAGE/MMCDA1: IC601.A4 (DAT1), R604.2; also elsewhere on the board
/EMMC_STORAGE/MMCDA2: IC601.A5 (DAT2), R603.2; also elsewhere on the board
/EMMC_STORAGE/MMCDA3: IC601.B2 (DAT3), R602.2; also elsewhere on the board
/EMMC_STORAGE/MMCDA4: IC601.B3 (DAT4), R601.2; also elsewhere on the board
/EMMC_STORAGE/MMCDA5: IC601.B4 (DAT5), R605.2; also elsewhere on the board
/EMMC_STORAGE/MMCDA6: IC601.B5 (DAT6), R606.2; also elsewhere on the board
/EMMC_STORAGE/MMCDA7: IC601.B6 (DAT7), R607.2; also elsewhere on the board
/EMMC_STORAGE/MMC_CLK: R609.2; also elsewhere on the board
/EMMC_STORAGE/MMC_CMD: R611.2; also elsewhere on the board
/EMMC_STORAGE/Vddim_eMMC: C613.1, C614.2, IC601.C2 (VDDIM)
GND: C601.2, C602.2, C603.1, C604.2, C605.1, C606.1, C607.1, C608.2, C609.2, C610.2, C611.2, C613.2, C614.1, IC601.A6 (VSS_1), IC601.C4 (VSSQ_1), IC601.E7 (VSS_2), IC601.G5 (VSS_3), IC601.H10 (VSS_4), IC601.J5 (VSS_5), IC601.K8 (VSS_6), IC601.N2 (VSSQ_2), IC601.N5 (VSSQ_3), IC601.P4 (VSSQ_4), IC601.P6 (VSSQ_5); also elsewhere on the board
unnamed: IC601.M6 (CLK), R609.1
unnamed: IC601.M5 (CMD), R611.1, R612.1
unnamed: IC601.H5 (DS), R613.1
unnamed: IC601.K5 (RST_N), R610.1

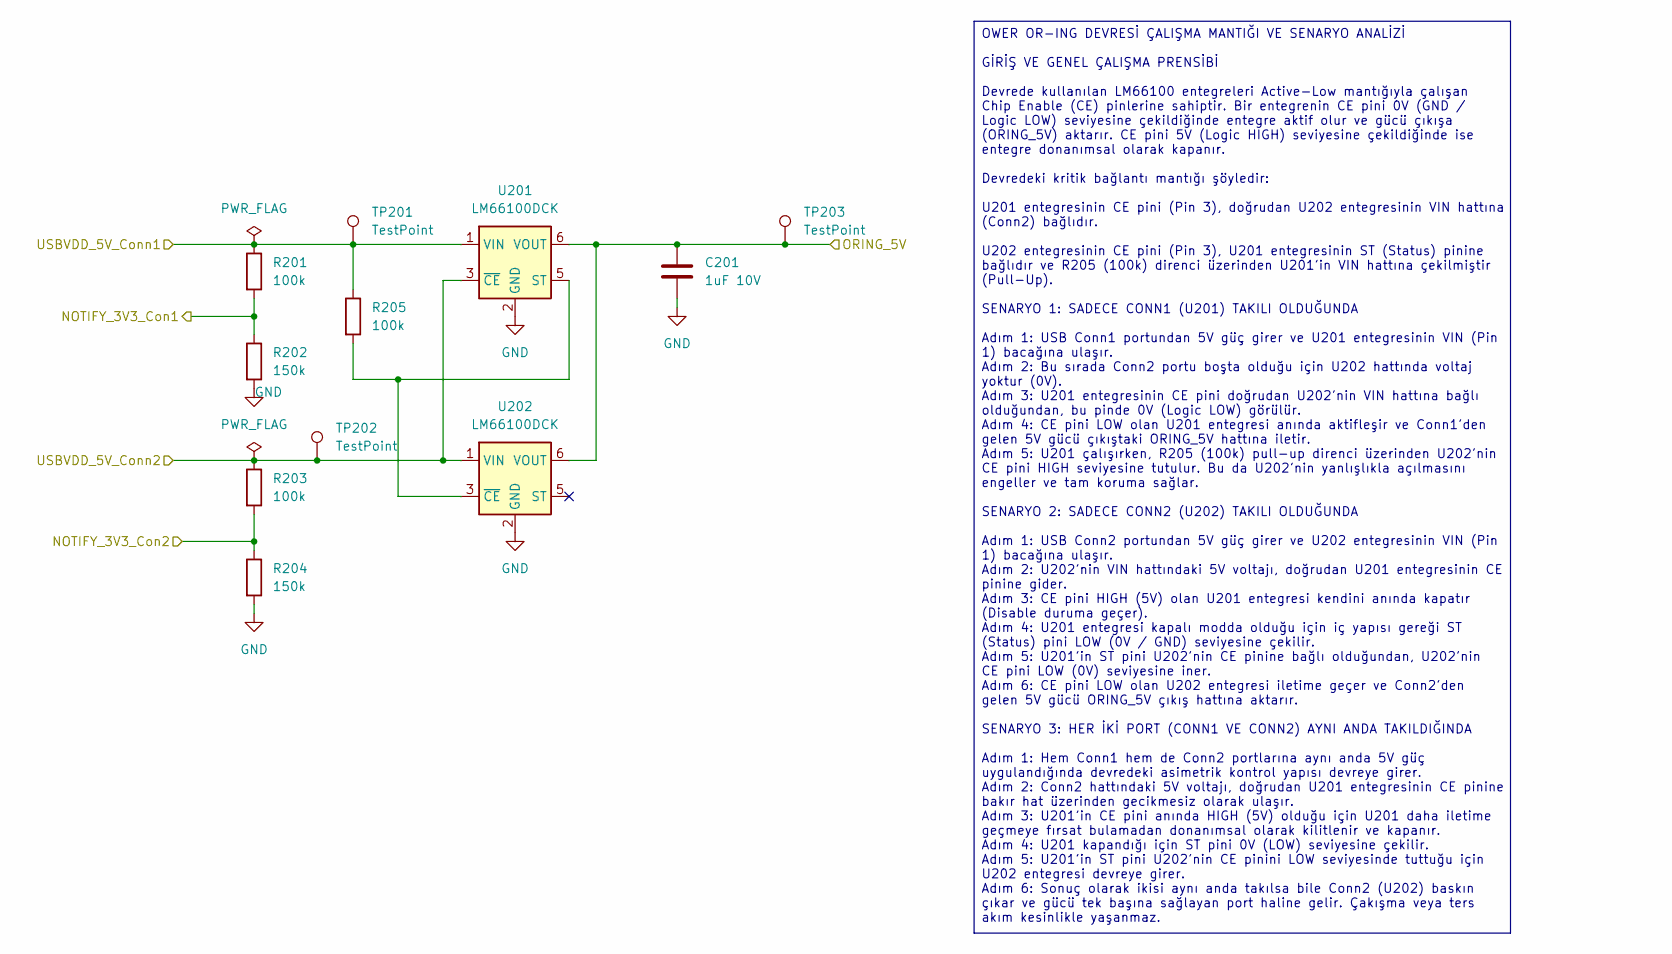
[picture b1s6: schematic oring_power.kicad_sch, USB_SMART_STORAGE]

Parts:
C201: 1uF 10V; C_0603_1608Metric
R201, R203, R205: 100k; R_0402_1005Metric
R202, R204: 150k; R_0402_1005Metric
TP201, TP202, TP203: TestPoint; TestPoint_Pad_D1.5mm
U201, U202: LM66100DCK; SOT-363_SC-70-6

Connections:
/ORING_POWER/NOTIFY_3V3_Con1: R201.2, R202.1; also elsewhere on the board
/ORING_POWER/NOTIFY_3V3_Con2: R203.2, R204.1; also elsewhere on the board
/ORING_POWER/ORING_5V: C201.1, TP203.1 (1_1), U201.6 (VOUT), U202.6 (VOUT); also elsewhere on the board
/VBUS_MCU: R203.1, TP202.1 (1_1), U201.3 (~CE), U202.1 (VIN); also elsewhere on the board
/VBUS_STORAGE: R201.1, R205.1, TP201.1 (1_1), U201.1 (VIN); also elsewhere on the board
GND: C201.2, R202.2, R204.2, U201.2 (GND), U202.2 (GND); also elsewhere on the board
unnamed: R205.2, U201.5 (ST), U202.3 (~CE)

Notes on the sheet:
OWER OR-ING DEVRESİ ÇALIŞMA MANTIĞI VE SENARYO ANALİZİ GİRİŞ VE GENEL ÇALIŞMA PRENSİBİ Devrede kullanılan LM66100 entegreleri Active-Low mantığıyla çalışan Chip Enable (CE) pinlerine sahiptir. Bir entegrenin CE pini 0V (GND / Logic LOW) seviyesine çekildiğinde entegre aktif olur ve gücü çıkışa (ORI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

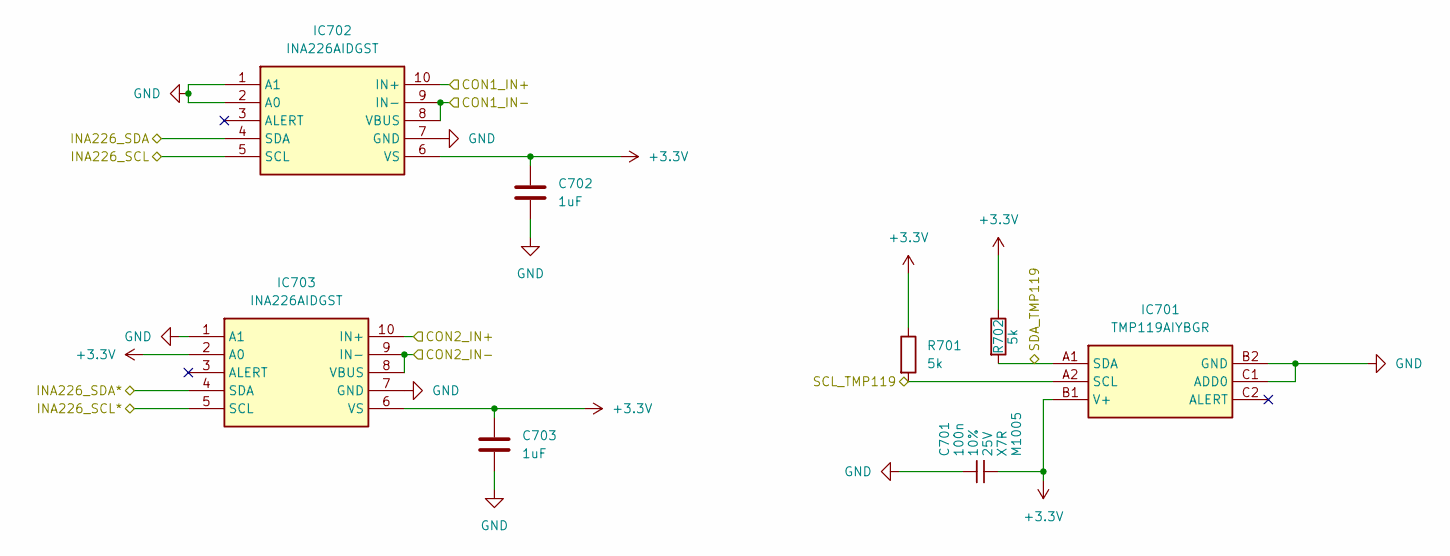
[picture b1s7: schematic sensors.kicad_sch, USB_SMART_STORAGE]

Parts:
C701: 100n; C_0402_1005Metric; voltage 25V; tolerance 10%; part_uid RP-01BJ9Y-KRGF41
C702: 1uF; C_0402_1005Metric
C703: 1uF; C_0603_1608Metric
IC701: TMP119AIYBGR; BGA6C40P2X3_95X149X52; Manufacturer_Part_Number TMP119AIYBGR; Mouser Part Number 595-TMP119AIYBGR
IC702, IC703: INA226AIDGST; SOP50P490X110-10N; Manufacturer_Part_Number INA226AIDGST; Mouser Part Number 595-INA226AIDGST
R701, R702: 5k; R_0402_1005Metric

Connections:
+3.3V: C701.2, C702.1, C703.1, IC701.B1 (V+), IC702.6 (VS), IC703.2 (A0), IC703.6 (VS), R701.1, R702.1; also elsewhere on the board
/RP2040/I2C0_SCL: IC701.A2 (SCL), IC702.5 (SCL), IC703.5 (SCL), R701.2; also elsewhere on the board
/RP2040/I2C0_SDA: IC701.A1 (SDA), IC702.4 (SDA), IC703.4 (SDA), R702.2; also elsewhere on the board
/VBUS_MCU__IN+: IC703.10 (IN+); also elsewhere on the board
/VBUS_MCU__IN-: IC703.8 (VBUS), IC703.9 (IN-); also elsewhere on the board
/VBUS_STORAGE_IN+: IC702.10 (IN+); also elsewhere on the board
/VBUS_STORAGE_IN-: IC702.8 (VBUS), IC702.9 (IN-); also elsewhere on the board
GND: C701.1, C702.2, C703.2, IC701.B2 (GND), IC701.C1 (ADD0), IC702.1 (A1), IC702.2 (A0), IC702.7 (GND), IC703.1 (A1), IC703.7 (GND); also elsewhere on the board
